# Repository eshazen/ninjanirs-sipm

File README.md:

# ninjanirs-sipm

Power supplies and electronics for SiPM-based optodes

Designs completed:

*  `KiCAD/lt3014-test` - test board with LT3014 voltage regulator
controlled by AD5270 digital pot, with INA201 current limiter
   * See [README](Testing/LT3014/README.md) for test details
* `KiCAD/sipm-hv-splitter` - candidate for in-system test
   * See [README](KiCAD/sipm-hv-splitter/README.md) for testing

Test logs:

* `Testing/LT3014` for the test board
* `Testing/sipm-splitter` for the splitter board

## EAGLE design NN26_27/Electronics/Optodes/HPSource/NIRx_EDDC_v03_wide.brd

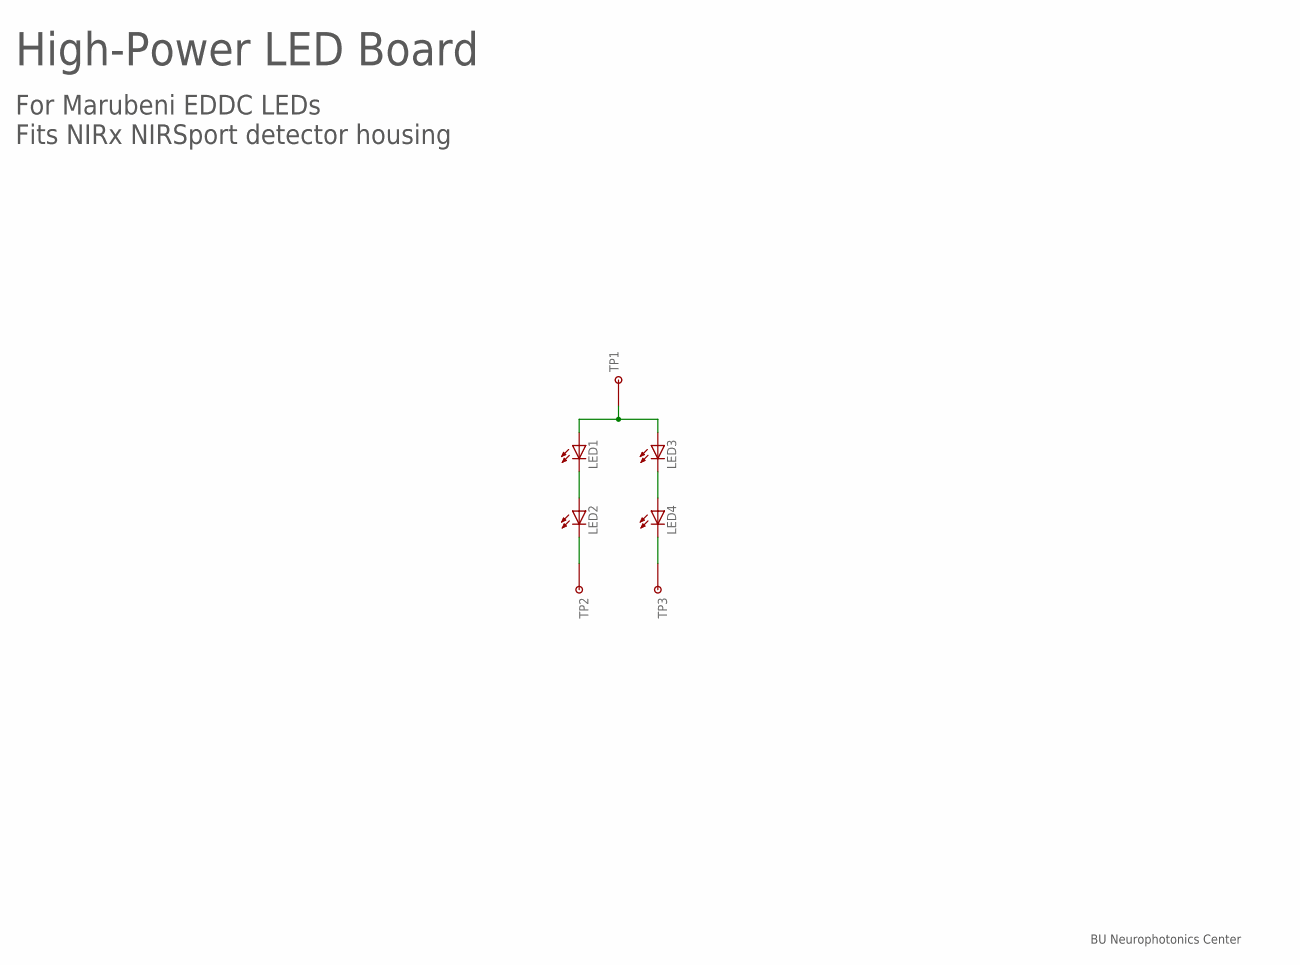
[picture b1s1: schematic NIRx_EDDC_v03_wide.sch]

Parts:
LED1, LED2, LED3, LED4: LED_EDCC; MARUBENI_EDCC
TP1, TP2, TP3: TESTPOINT_PADMEDIUM; TESTPAD_MEDIUM

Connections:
76: LED2.C, TP2.P$1
85: LED4.C, TP3.P$1
AN: LED1.A, LED3.A, TP1.P$1
I76: LED1.C, LED2.A
I85: LED3.C, LED4.A

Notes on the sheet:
High-Power LED Board
For Marubeni EDDC LEDs Fits NIRx NIRSport detector housing
BU Neurophotonics Center

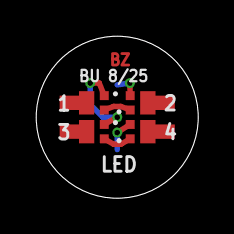
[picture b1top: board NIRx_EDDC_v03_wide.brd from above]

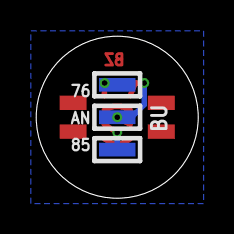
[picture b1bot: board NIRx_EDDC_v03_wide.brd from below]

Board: 2 copper layers, 9.0 x 9.0 mm, 7 parts (3 on the bottom side), 5 nets.

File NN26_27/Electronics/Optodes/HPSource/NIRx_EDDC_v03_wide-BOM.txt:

LED1, LED2: Marubeni EDCC760D-1100
LED3, LED4: Marubeni EDCC850D-1100

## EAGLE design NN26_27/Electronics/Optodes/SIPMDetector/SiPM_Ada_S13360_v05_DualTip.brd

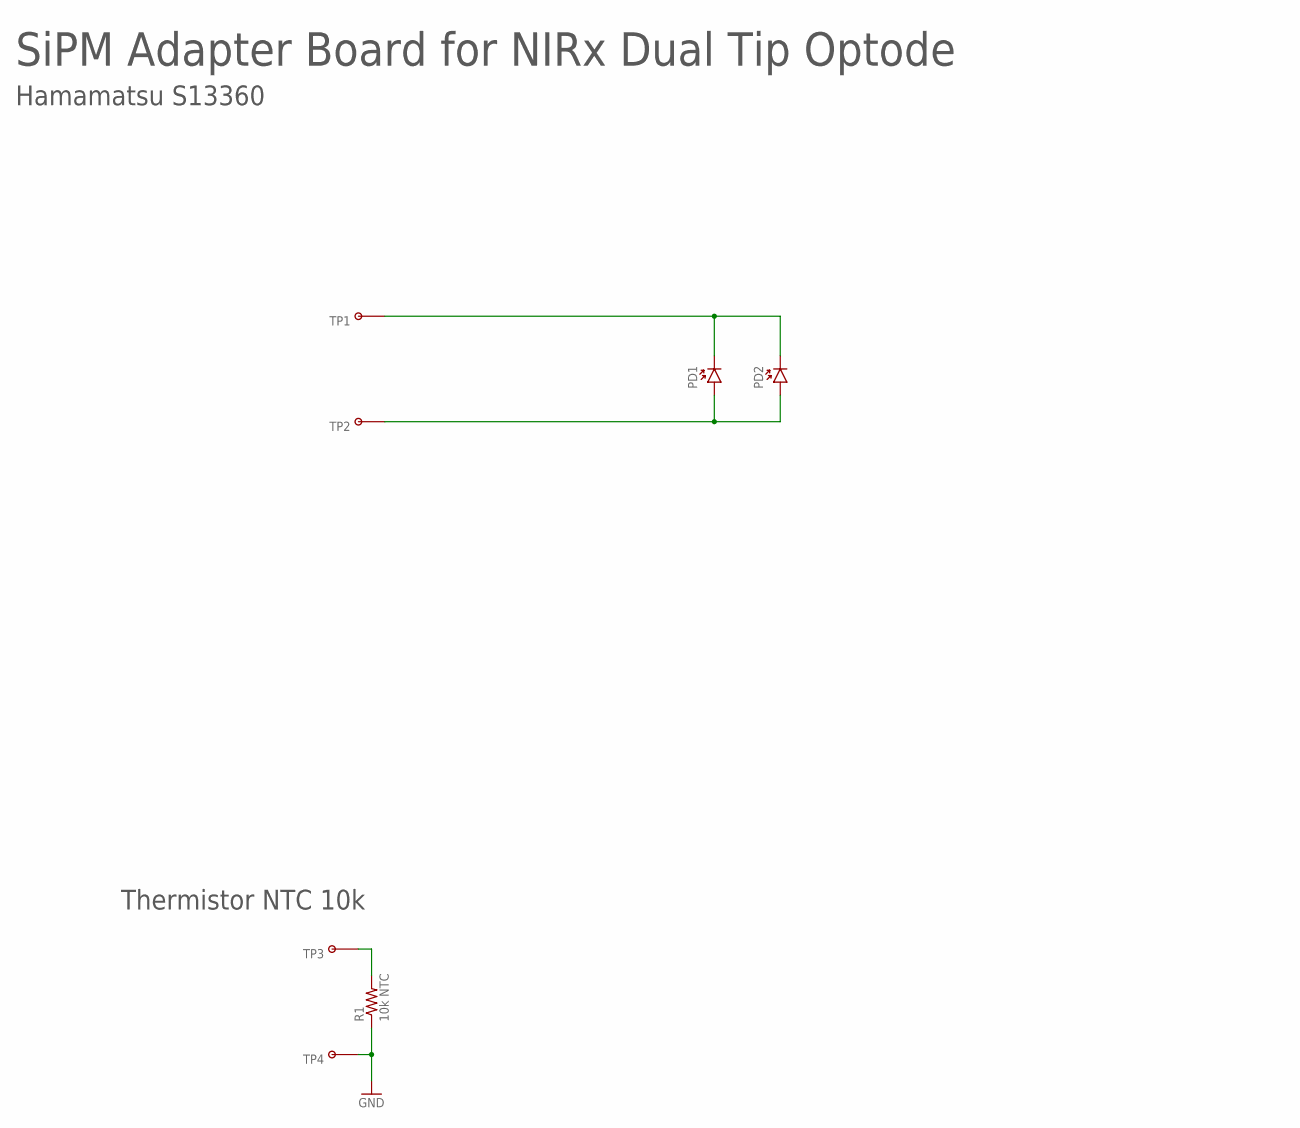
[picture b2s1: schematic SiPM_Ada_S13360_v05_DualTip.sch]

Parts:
PD1, PD2: PHOTODIODE_S13360-30XXPE; S13360-30XXPE
R1: 10k NTC; 0603-RES
TP1, TP2, TP3, TP4: TESTPOINT_PADMEDIUM; TESTPAD_MEDIUM

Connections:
A: PD1.A, PD2.A, TP2.P$1
C: PD1.C, PD2.C, TP1.P$1
GND: R1.1, TP4.P$1
T: R1.2, TP3.P$1

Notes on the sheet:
SiPM Adapter Board for NIRx Dual Tip Optode
Hamamatsu S13360
Thermistor NTC 10k

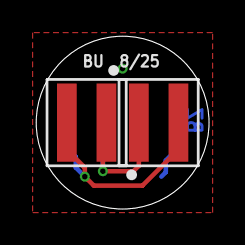
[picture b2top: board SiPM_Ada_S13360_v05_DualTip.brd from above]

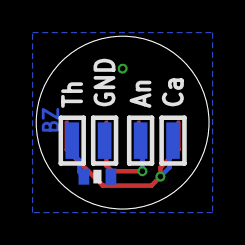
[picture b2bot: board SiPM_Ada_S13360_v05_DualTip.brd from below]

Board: 2 copper layers, 9.6 x 9.6 mm, 7 parts (5 on the bottom side), 4 nets.

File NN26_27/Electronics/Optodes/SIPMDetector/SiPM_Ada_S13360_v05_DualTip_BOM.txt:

PD1, PD2: Hamamatsu S13360-3050PE
R1: NTCG163JF103FT1
TP1, TP2, TP3, TP4: DNP (wire solder pads)

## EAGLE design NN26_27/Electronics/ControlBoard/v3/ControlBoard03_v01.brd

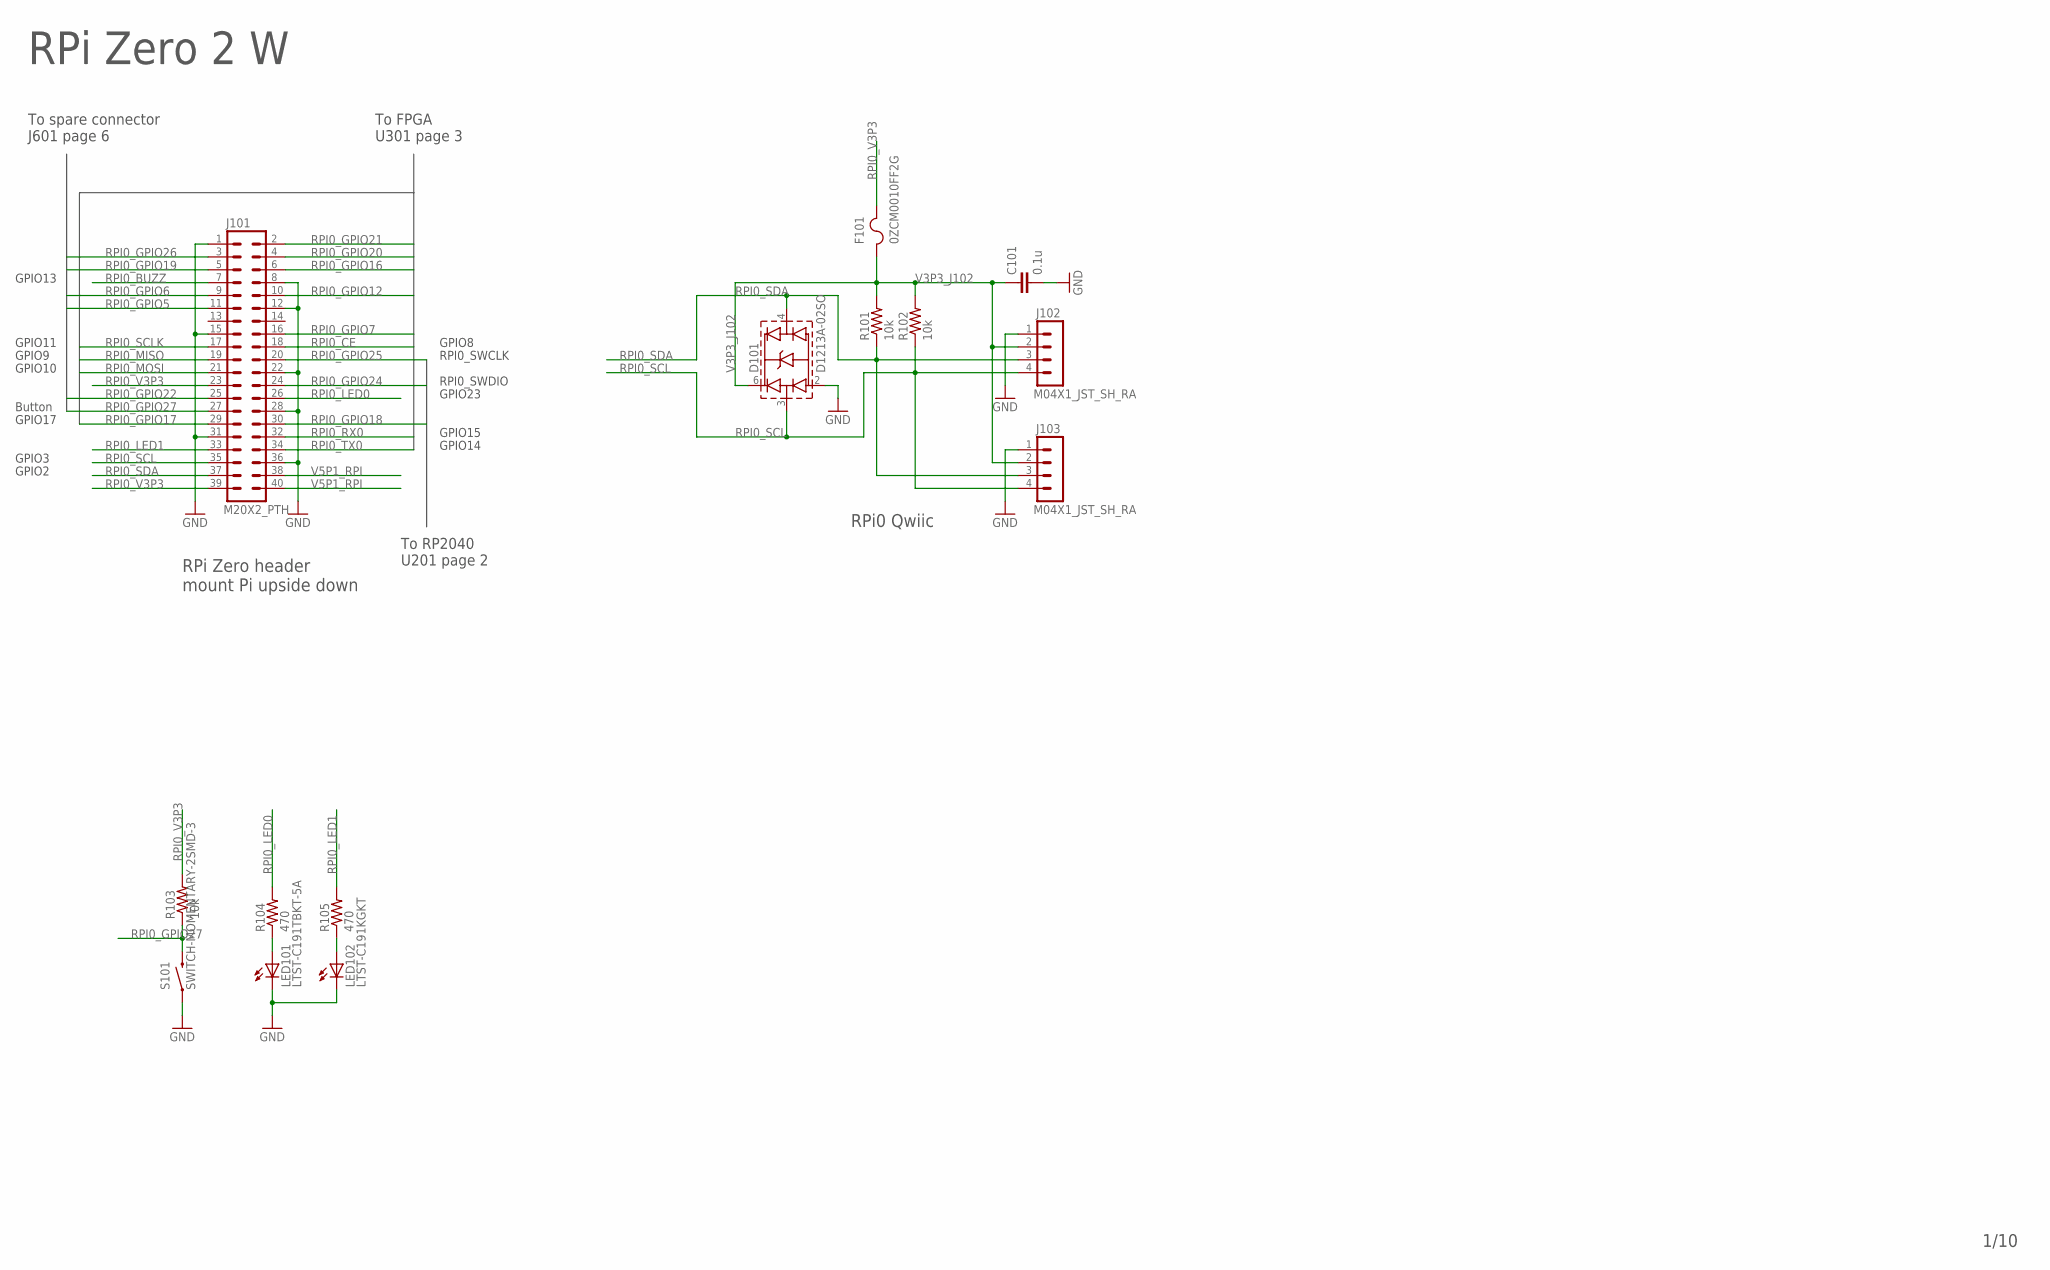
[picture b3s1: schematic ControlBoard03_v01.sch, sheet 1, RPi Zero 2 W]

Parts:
C101: 0.1u; 0402-CAP
D101: D1213A-02SO; SOT23-6
F101: 0ZCM0010FF2G; 0603-RES
J101: M20X2_PTH
J102, J103: M04X1_JST_SH_RA; M04X1_JST_SH_SM_RA
LED101: LTST-C191TBKT-5A; LED-0603
LED102: LTST-C191KGKT; LED-0603
R101, R102, R103: 10k; 0402-RES
R104, R105: 470; 0402-RES
S101: SWITCH-MOMENTARY-2SMD-3; TACTILE_SWITCH_SMD-3

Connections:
GND: C101.2, D101.2 (VN), J101.1, J101.8, J101.12, J101.15, J101.22, J101.28, J101.31, J101.36, J102.1, J103.1, LED101.C, LED102.C, S101.1; also elsewhere on the board
unnamed: LED101.A, R104.1
unnamed: LED102.A, R105.1
RPI0_BUZZ: J101.7; also elsewhere on the board
RPI0_CE: J101.18; also elsewhere on the board
RPI0_GPIO5: J101.11; also elsewhere on the board
RPI0_GPIO6: J101.9; also elsewhere on the board
RPI0_GPIO7: J101.16; also elsewhere on the board
RPI0_GPIO12: J101.10; also elsewhere on the board
RPI0_GPIO16: J101.6; also elsewhere on the board
RPI0_GPIO17: J101.29; also elsewhere on the board
RPI0_GPIO18: J101.30; also elsewhere on the board
RPI0_GPIO19: J101.5; also elsewhere on the board
RPI0_GPIO20: J101.4; also elsewhere on the board
RPI0_GPIO21: J101.2; also elsewhere on the board
RPI0_GPIO22: J101.25; also elsewhere on the board
RPI0_GPIO24: J101.24; also elsewhere on the board
RPI0_GPIO25: J101.20; also elsewhere on the board
RPI0_GPIO26: J101.3; also elsewhere on the board
RPI0_GPIO27: J101.27, R103.1, S101.4 (2); also elsewhere on the board
RPI0_LED0: J101.26, R104.2
RPI0_LED1: J101.33, R105.2
RPI0_MISO: J101.19; also elsewhere on the board
RPI0_MOSI: J101.21; also elsewhere on the board
RPI0_RX0: J101.32; also elsewhere on the board
RPI0_SCL: D101.3 (CH1), J101.35, J102.4, J103.4, R102.1; also elsewhere on the board
RPI0_SCLK: J101.17; also elsewhere on the board
RPI0_SDA: D101.4 (CH2), J101.37, J102.3, J103.3, R101.1; also elsewhere on the board
RPI0_TX0: J101.34; also elsewhere on the board
RPI0_V3P3: F101.2, J101.23, J101.39, R103.2
V3P3_J102: C101.1, D101.6 (VP), F101.1, J102.2, J103.2, R101.2, R102.2
V5P1_RPI: J101.38, J101.40; also elsewhere on the board

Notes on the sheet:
GPIO15
GPIO14
RPI0_SWDIO
RPI0_SWCLK
GPIO8
GPIO11
GPIO9
GPIO10
GPIO2
GPIO3
GPIO13
RPi Zero 2 W
RPi Zero header mount Pi upside down
RPi0 Qwiic
GPIO23
Button
To spare connector J601 page 6
To FPGA U301 page 3
To RP2040 U201 page 2
GPIO17

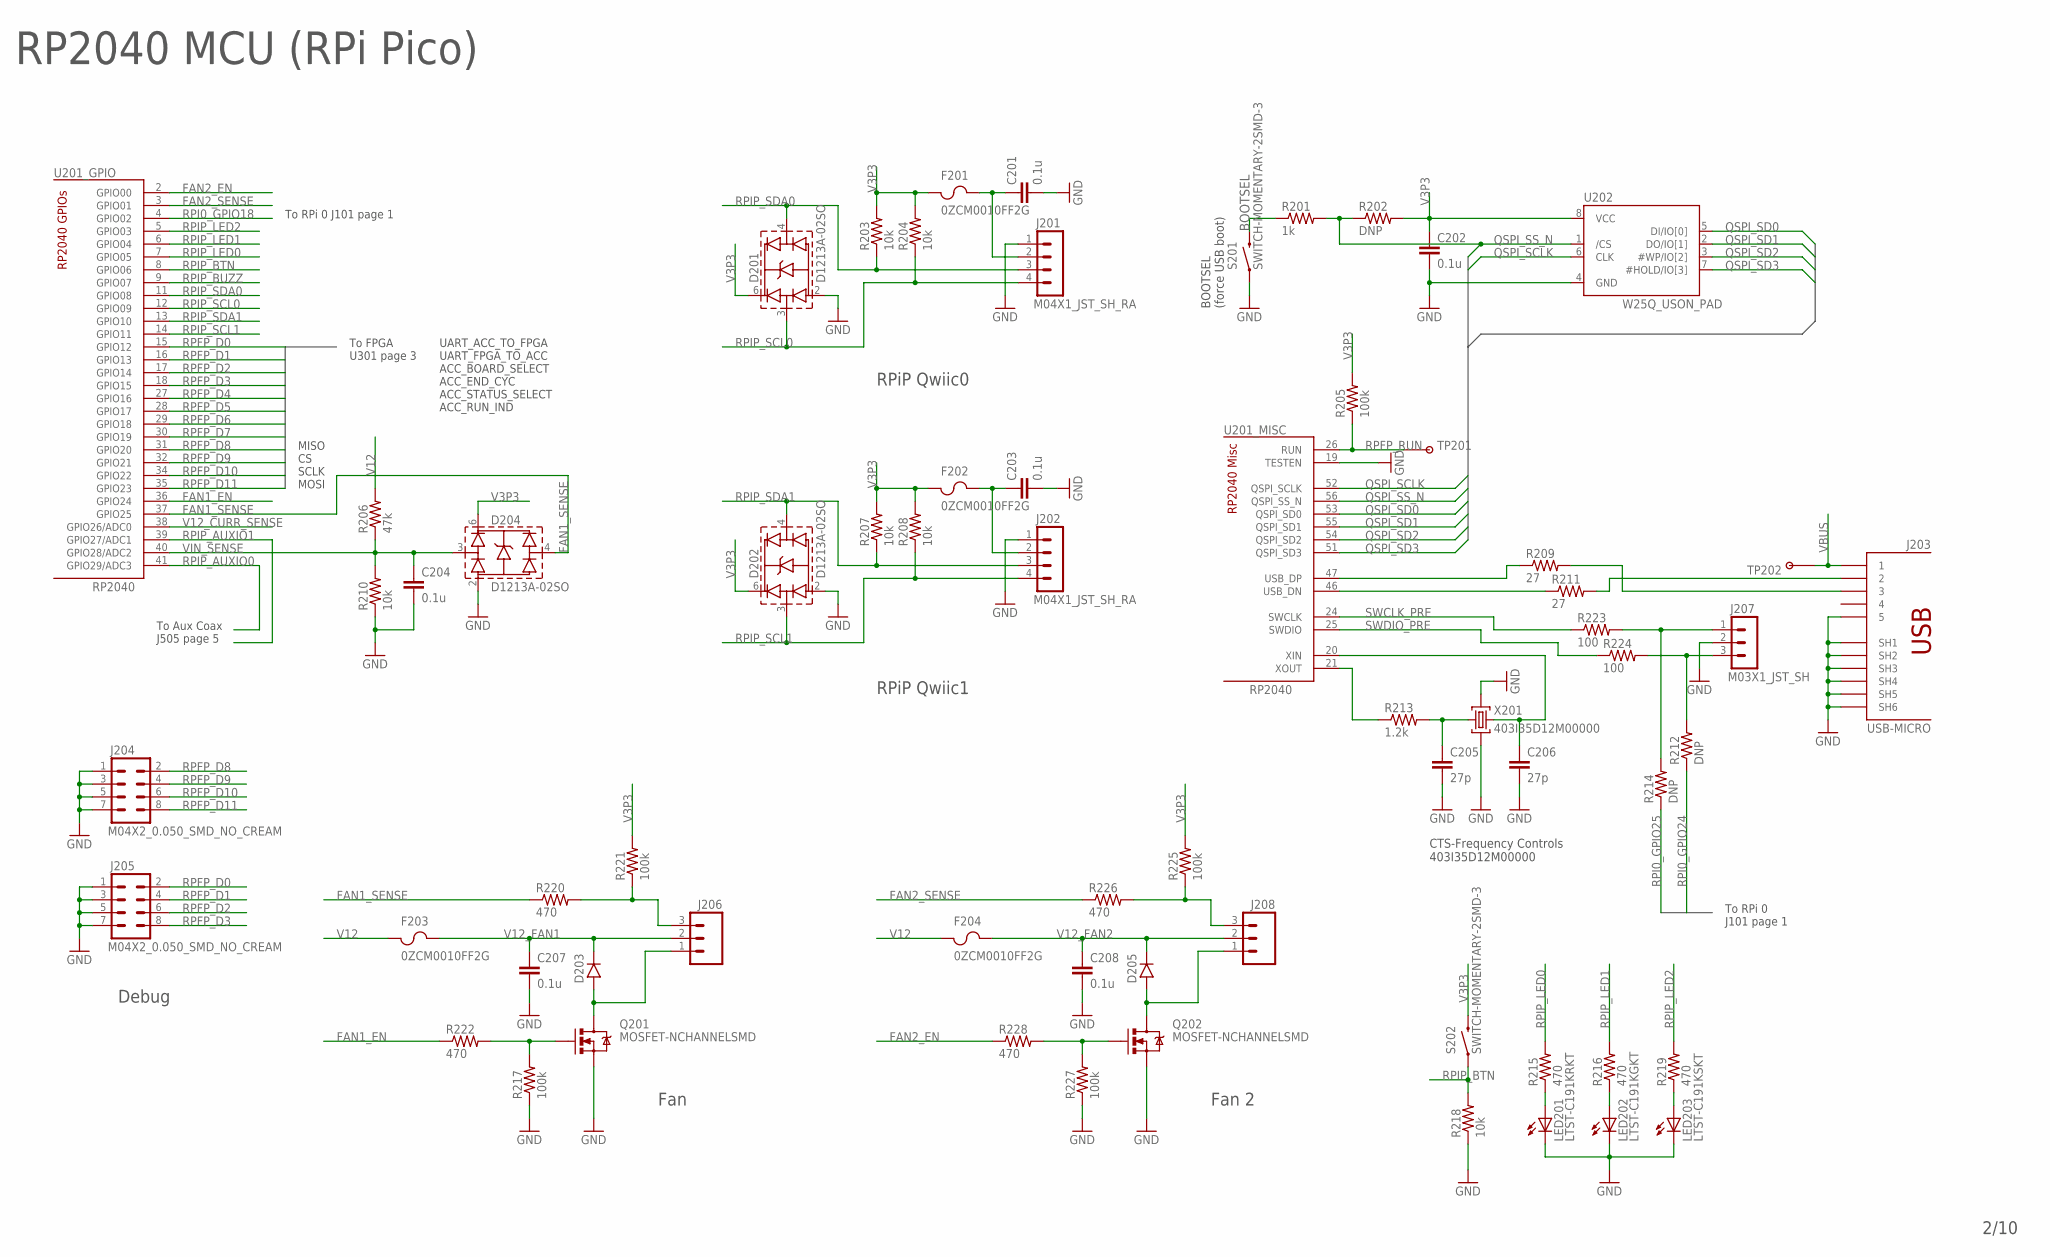
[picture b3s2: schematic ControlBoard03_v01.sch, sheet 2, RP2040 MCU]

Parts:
C201, C202, C203, C204, C207, C208: 0.1u; 0402-CAP
C205, C206: 27p; 0402-CAP
D201, D202, D204: D1213A-02SO; SOT23-6
D203, D205: DIODE_SOD523; SOD523
F201, F202, F203, F204: 0ZCM0010FF2G; 0603-RES
J201, J202: M04X1_JST_SH_RA; M04X1_JST_SH_SM_RA
J203: USB-MICRO
J204, J205: M04X2_0.050_SMD_NO_CREAM
J206, J208: M03POLAR; MOLEX-1X3
J207: M03X1_JST_SH; M03X1_JST_SH_SM
LED201: LTST-C191KRKT; LED-0603
LED202: LTST-C191KGKT; LED-0603
LED203: LTST-C191KSKT; LED-0603
Q201, Q202: MOSFET-NCHANNELSMD; SOT23-3
R201: 1k; 0402-RES
R202, R212, R214: DNP; 0402-RES
R203, R204, R207, R208, R210, R218: 10k; 0402-RES
R205, R217, R221, R225, R227: 100k; 0402-RES
R206: 47k; 0402-RES
R209, R211: 27; 0402-RES
R213: 1.2k; 0402-RES
R215, R216, R219, R220, R222, R226, R228: 470; 0402-RES
R223, R224: 100; 0402-RES
S201, S202: SWITCH-MOMENTARY-2SMD-3; TACTILE_SWITCH_SMD-3
TP201, TP202: TESTPOINT_ROUND; TESTPAD_ROUND
U201: RP2040; QFN-56_EP
U202: W25Q_USON_PAD; USON8L-2X3MM_APM
X201: 403I35D12M00000; CRYSTAL-3.2-2.5

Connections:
BOOTSEL: R201.1, S201.4 (2)
FAN1_EN: R222.1, U201.36 (GPIO24)
FAN1_SENSE: D204.4 (CH2), R220.1, U201.37 (GPIO25)
FAN2_EN: R228.1, U201.2 (GPIO00)
FAN2_SENSE: R226.1, U201.3 (GPIO01)
GND: C201.2, C202.2, C203.2, C204.2, C205.2, C206.2, C207.2, C208.2, D201.2 (VN), D202.2 (VN), D204.2 (VN), J201.1, J202.1, J203.5, J203.SH1, J203.SH2, J203.SH3, J203.SH4, J203.SH5, J203.SH6, J204.1, J204.3, J204.5, J204.7, J205.1, J205.3, J205.5, J205.7, J207.2, LED201.C, LED202.C, LED203.C, Q201.2 (S), Q202.2 (S), R210.1, R217.1, R218.1, R227.1, S201.1, U201.19 (TESTEN), U202.4 (GND), X201.2 (GND), X201.4 (GND); also elsewhere on the board
unnamed: C206.1, U201.20 (XIN), X201.3 (C2)
unnamed: C205.1, R213.2, X201.1 (C1)
unnamed: R213.1, U201.21 (XOUT)
unnamed: R209.1, U201.47 (USB_DP)
unnamed: R211.1, U201.46 (USB_DN)
unnamed: J203.2, R211.2
unnamed: J203.3, R209.2
unnamed: LED203.A, R219.1
unnamed: J206.3, R220.2, R221.1
unnamed: LED202.A, R216.1
unnamed: LED201.A, R215.1
unnamed: D203.A, J206.1, Q201.3 (D)
unnamed: Q201.1 (G), R217.2, R222.2
unnamed: D205.A, J208.1, Q202.3 (D)
unnamed: J208.3, R225.1, R226.2
unnamed: Q202.1 (G), R227.2, R228.2
QSPI_SCLK: U201.52 (QSPI_SCLK), U202.6 (CLK)
QSPI_SD0: U201.53 (QSPI_SD0), U202.5 (DI/IO[0])
QSPI_SD1: U201.55 (QSPI_SD1), U202.2 (DO/IO[1])
QSPI_SD2: U201.54 (QSPI_SD2), U202.3 (#WP/IO[2])
QSPI_SD3: U201.51 (QSPI_SD3), U202.7 (#HOLD/IO[3])
QSPI_SS_N: R201.2, R202.1, U201.56 (QSPI_SS_N), U202.1 (/CS)
RPFP_D0: J205.2, U201.15 (GPIO12); also elsewhere on the board
RPFP_D1: J205.4, U201.16 (GPIO13); also elsewhere on the board
RPFP_D2: J205.6, U201.17 (GPIO14); also elsewhere on the board
RPFP_D3: J205.8, U201.18 (GPIO15); also elsewhere on the board
RPFP_D4: U201.27 (GPIO16); also elsewhere on the board
RPFP_D5: U201.28 (GPIO17); also elsewhere on the board
RPFP_D6: U201.29 (GPIO18); also elsewhere on the board
RPFP_D7: U201.30 (GPIO19); also elsewhere on the board
RPFP_D8: J204.2, U201.31 (GPIO20); also elsewhere on the board
RPFP_D9: J204.4, U201.32 (GPIO21); also elsewhere on the board
RPFP_D10: J204.6, U201.34 (GPIO22); also elsewhere on the board
RPFP_D11: J204.8, U201.35 (GPIO23); also elsewhere on the board
RPFP_RUN: R205.1, TP201.P$1, U201.26 (RUN); also elsewhere on the board
RPI0_GPIO18: U201.4 (GPIO02); also elsewhere on the board
RPI0_GPIO24: R212.1; also elsewhere on the board
RPI0_GPIO25: R214.1; also elsewhere on the board
RPIP_AUXIO0: U201.41 (GPIO29/ADC3); also elsewhere on the board
RPIP_AUXIO1: U201.39 (GPIO27/ADC1); also elsewhere on the board
RPIP_BTN: R218.2, S202.1, U201.8 (GPIO06)
RPIP_BUZZ: U201.9 (GPIO07); also elsewhere on the board
RPIP_LED0: R215.2, U201.7 (GPIO05)
RPIP_LED1: R216.2, U201.6 (GPIO04)
RPIP_LED2: R219.2, U201.5 (GPIO03)
RPIP_SCL0: D201.3 (CH1), J201.4, R204.1, U201.12 (GPIO09)
RPIP_SCL1: D202.3 (CH1), J202.4, R208.1, U201.14 (GPIO11); also elsewhere on the board
RPIP_SDA0: D201.4 (CH2), J201.3, R203.1, U201.11 (GPIO08)
RPIP_SDA1: D202.4 (CH2), J202.3, R207.1, U201.13 (GPIO10); also elsewhere on the board
SWCLK: J207.1, R214.2, R223.2
SWCLK_PRE: R223.1, U201.24 (SWCLK)
SWDIO: J207.3, R212.2, R224.2
SWDIO_PRE: R224.1, U201.25 (SWDIO)
V3P3: C202.1, D201.6 (VP), D202.6 (VP), D204.6 (VP), F201.1, F202.1, R202.2, R203.2, R204.2, R205.2, R207.2, R208.2, R221.2, R225.2, S202.4 (2), U202.8 (VCC); also elsewhere on the board
V3P3_J201: C201.1, F201.2, J201.2
V3P3_J202: C203.1, F202.2, J202.2
V12: F203.1, F204.1, R206.2; also elsewhere on the board
V12_CURR_SENSE: U201.38 (GPIO26/ADC0); also elsewhere on the board
V12_FAN1: C207.1, D203.C, F203.2, J206.2
V12_FAN2: C208.1, D205.C, F204.2, J208.2
VBUS: J203.1, TP202.P$1
VIN_SENSE: C204.1, D204.3 (CH1), R206.1, R210.2, U201.40 (GPIO28/ADC2)

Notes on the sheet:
BOOTSEL (force USB boot)
CTS-Frequency Controls 403I35D12M00000
RP2040 MCU (RPi Pico)
RPiP Qwiic0
RPiP Qwiic1
Debug
To RPi 0 J101 page 1
To RPi 0 J101 page 1
To FPGA U301 page 3
To Aux Coax J505 page 5
MISO
SCLK
MOSI
UART_ACC_TO_FPGA
UART_FPGA_TO_ACC
ACC_BOARD_SELECT
ACC_END_CYC
ACC_STATUS_SELECT
ACC_RUN_IND
Fan
Fan 2

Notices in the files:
parts and their libraries:
SparkFun-Connectors: Licensing: Creative Commons ShareAlike 4.0 International - https://creativecommons.org/licenses/by-sa/4.0
